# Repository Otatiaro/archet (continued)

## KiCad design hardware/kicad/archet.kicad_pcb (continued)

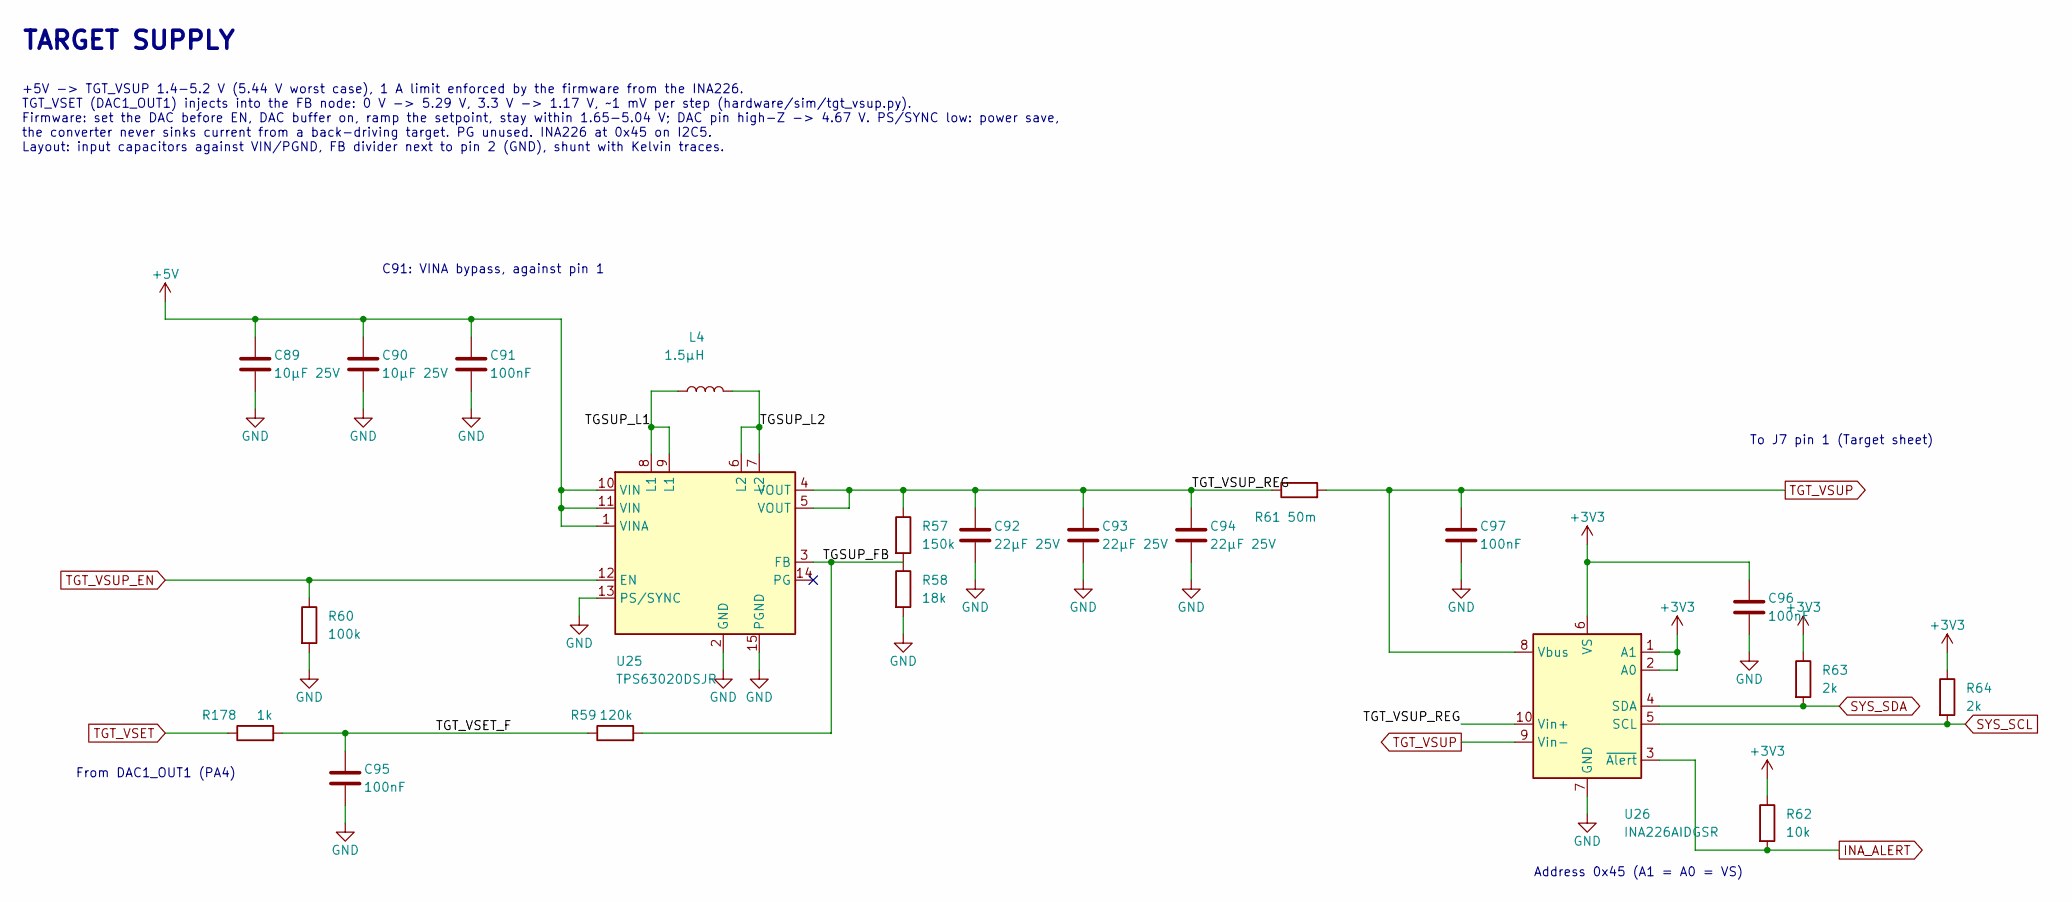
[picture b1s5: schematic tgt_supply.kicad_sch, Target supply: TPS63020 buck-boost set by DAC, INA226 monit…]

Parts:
C89, C90: 10µF 25V; C_0805_2012Metric; LCSC C15850
C91, C95, C96, C97: 100nF; C_0402_1005Metric; LCSC C307331
C92, C93, C94: 22µF 25V; C_1206_3216Metric; LCSC C12891
L4: 1.5µH; L_Changjiang_FXL0420; LCSC C167205
R57: 150k; R_0402_1005Metric; LCSC C25755
R58: 18k; R_0402_1005Metric; LCSC C25762
R59: 120k; R_0402_1005Metric; LCSC C25750
R60: 100k; R_0402_1005Metric; LCSC C25741
R61: 50m; R_1206_3216Metric; LCSC C844686
R62: 10k; R_0402_1005Metric; LCSC C25744
R63, R64: 2k; R_0402_1005Metric; LCSC C4109
R178: 1k; R_0402_1005Metric; LCSC C11702
U25: TPS63020DSJR; Texas_DSJ0014A_VSON-14_3x4mm_P0.5mm; LCSC C15483
U26: INA226AIDGSR; TSSOP-10_3x3mm_P0.5mm; LCSC C49851

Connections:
+3V3: C96.1, R62.1, R63.1, R64.1, U26.1 (A1), U26.2 (A0), U26.6 (VS); also elsewhere on the board
+5V: C89.1, C90.1, C91.1, U25.1 (VINA), U25.10 (VIN), U25.11 (VIN); also elsewhere on the board
/Target supply/TGSUP_FB: R57.2, R58.1, R59.2, U25.3 (FB)
/Target supply/TGSUP_L1: L4.1, U25.8 (L1), U25.9 (L1)
/Target supply/TGSUP_L2: L4.2, U25.6 (L2), U25.7 (L2)
/Target supply/TGT_VSET_F: C95.1, R59.1, R178.2
/Target supply/TGT_VSUP_REG: C92.1, C93.1, C94.1, R57.1, R61.1, U25.4 (VOUT), U25.5 (VOUT), U26.10 (Vin+)
GND: C89.2, C90.2, C91.2, C92.2, C93.2, C94.2, C95.2, C96.2, C97.2, R58.2, R60.2, U25.2 (GND), U25.13 (PS/SYNC), U25.15 (PGND), U26.7 (GND); also elsewhere on the board
INA_ALERT: R62.2, U26.3 (~Alert); also elsewhere on the board
SYS_SCL: R64.2, U26.5 (SCL); also elsewhere on the board
SYS_SDA: R63.2, U26.4 (SDA); also elsewhere on the board
TGT_VSET: R178.1; also elsewhere on the board
TGT_VSUP: C97.1, R61.2, U26.8 (Vbus), U26.9 (Vin-); also elsewhere on the board
TGT_VSUP_EN: R60.1, U25.12 (EN); also elsewhere on the board

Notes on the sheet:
TARGET SUPPLY
+5V -> TGT_VSUP 1.4-5.2 V (5.44 V worst case), 1 A limit enforced by the firmware from the INA226. TGT_VSET (DAC1_OUT1) injects into the FB node: 0 V -> 5.29 V, 3.3 V -> 1.17 V, ~1 mV per step (hardware/sim/tgt_vsup.py). Firmware: set the DAC before EN, DAC buffer on, ramp the setpoint, stay within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
C91: VINA bypass, against pin 1
From DAC1_OUT1 (PA4)
To J7 pin 1 (Target sheet)
Address 0x45 (A1 = A0 = VS)

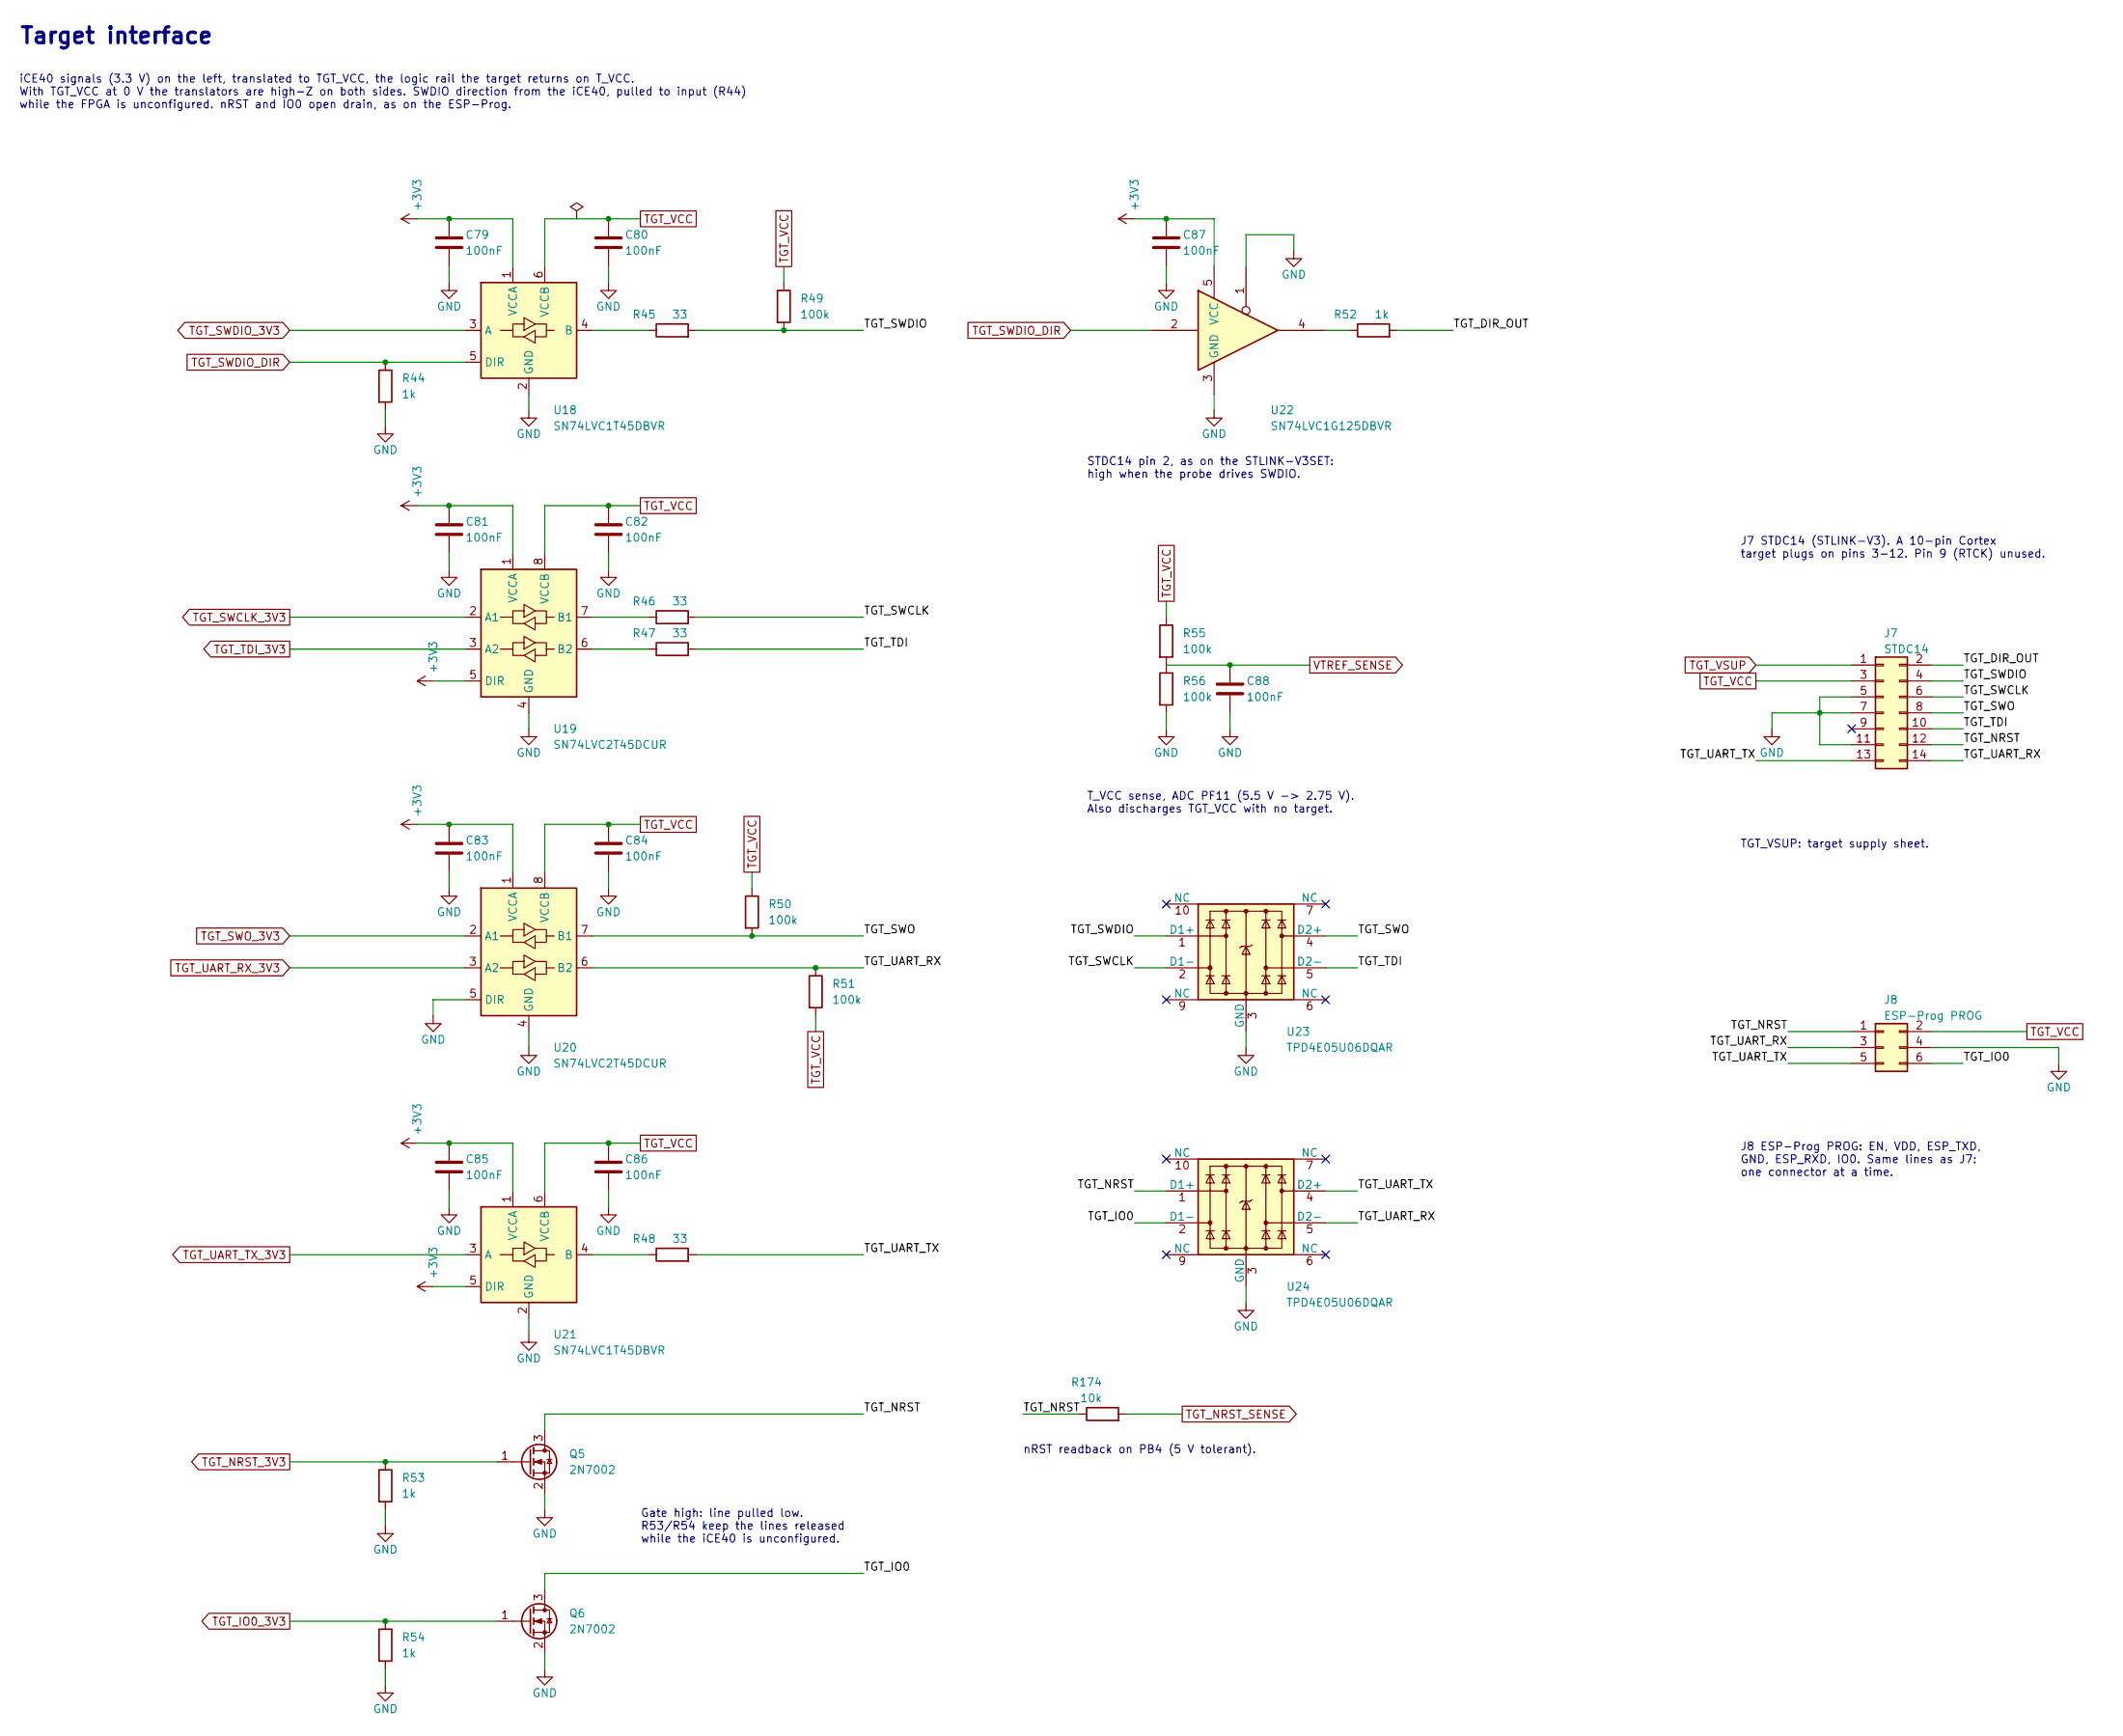
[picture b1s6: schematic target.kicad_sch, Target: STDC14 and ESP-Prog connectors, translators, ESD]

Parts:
C79, C80, C81, C82, C83, C84, C85, C86, C87, C88: 100nF; C_0402_1005Metric; LCSC C307331
J7: STDC14; FTSH-107-01-L-DV-K; LCSC C5307809
J8: ESP-Prog PROG; PinHeader_2x03_P2.54mm_Vertical; LCSC C492420
Q5, Q6: 2N7002; SOT-23; LCSC C8545
R44, R52, R53, R54: 1k; R_0402_1005Metric; LCSC C11702
R45, R46, R47, R48: 33; R_0402_1005Metric; LCSC C25105
R49, R50, R51, R55, R56: 100k; R_0402_1005Metric; LCSC C25741
R174: 10k; R_0402_1005Metric; LCSC C25744
U18, U21: SN74LVC1T45DBVR; SOT-23-6; LCSC C7843
U19, U20: SN74LVC2T45DCUR; VSSOP-8_2.3x2mm_P0.5mm; LCSC C15741
U22: SN74LVC1G125DBVR; SOT-23-5; LCSC C23654
U23, U24: TPD4E05U06DQAR; USON-10_2.5x1.0mm_P0.5mm; LCSC C138714

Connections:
+3V3: C79.1, C81.1, C83.1, C85.1, C87.1, U18.1 (VCCA), U19.1 (VCCA), U19.5 (DIR), U20.1 (VCCA), U21.1 (VCCA), U21.5 (DIR), U22.5 (VCC); also elsewhere on the board
/Target/TGT_DIR_OUT: J7.2, R52.2
/Target/TGT_IO0: J8.6, Q6.3 (D), U24.2 (D1-)
/Target/TGT_NRST: J7.12, J8.1, Q5.3 (D), R174.1, U24.1 (D1+)
/Target/TGT_SWCLK: J7.6, R46.2, U23.2 (D1-)
/Target/TGT_SWDIO: J7.4, R45.2, R49.2, U23.1 (D1+)
/Target/TGT_SWO: J7.8, R50.2, U20.7 (B1), U23.4 (D2+)
/Target/TGT_TDI: J7.10, R47.2, U23.5 (D2-)
/Target/TGT_UART_RX: J7.14, J8.3, R51.1, U20.6 (B2), U24.5 (D2-)
/Target/TGT_UART_TX: J7.13, J8.5, R48.2, U24.4 (D2+)
GND: C79.2, C80.2, C81.2, C82.2, C83.2, C84.2, C85.2, C86.2, C87.2, C88.2, J7.5, J7.7, J7.11, J8.4, Q5.2 (S), Q6.2 (S), R44.2, R53.2, R54.2, R56.2, U18.2 (GND), U19.4 (GND), U20.4 (GND), U20.5 (DIR), U21.2 (GND), U22.1, U22.3 (GND), U23.3 (GND), U23.8 (GND), U24.3 (GND), U24.8 (GND); also elsewhere on the board
unnamed: R52.1, U22.4
unnamed: R45.1, U18.4 (B)
unnamed: R46.1, U19.7 (B1)
unnamed: R47.1, U19.6 (B2)
unnamed: R48.1, U21.4 (B)
TGT_IO0_3V3: Q6.1 (G), R54.1; also elsewhere on the board
TGT_NRST_3V3: Q5.1 (G), R53.1; also elsewhere on the board
TGT_NRST_SENSE: R174.2; also elsewhere on the board
TGT_SWCLK_3V3: U19.2 (A1); also elsewhere on the board
TGT_SWDIO_3V3: U18.3 (A); also elsewhere on the board
TGT_SWDIO_DIR: R44.1, U18.5 (DIR), U22.2; also elsewhere on the board
TGT_SWO_3V3: U20.2 (A1); also elsewhere on the board
TGT_TDI_3V3: U19.3 (A2); also elsewhere on the board
TGT_UART_RX_3V3: U20.3 (A2); also elsewhere on the board
TGT_UART_TX_3V3: U21.3 (A); also elsewhere on the board
TGT_VCC: C80.1, C82.1, C84.1, C86.1, J7.3, J8.2, R49.1, R50.1, R51.2, R55.1, U18.6 (VCCB), U19.8 (VCCB), U20.8 (VCCB), U21.6 (VCCB)
TGT_VSUP: J7.1; also elsewhere on the board
VTREF_SENSE: C88.1, R55.2, R56.1; also elsewhere on the board

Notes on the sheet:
Target interface
iCE40 signals (3.3 V) on the left, translated to TGT_VCC, the logic rail the target returns on T_VCC. With TGT_VCC at 0 V the translators are high-Z on both sides. SWDIO direction from the iCE40, pulled to input (R44) while the FPGA is unconfigured. nRST and IO0 open drain, as on the ESP-Prog.
Gate high: line pulled low. R53/R54 keep the lines released while the iCE40 is unconfigured.
nRST readback on PB4 (5 V tolerant).
STDC14 pin 2, as on the STLINK-V3SET: high when the probe drives SWDIO.
T_VCC sense, ADC PF11 (5.5 V -> 2.75 V). Also discharges TGT_VCC with no target.
J7 STDC14 (STLINK-V3). A 10-pin Cortex target plugs on pins 3-12. Pin 9 (RTCK) unused.
J8 ESP-Prog PROG: EN, VDD, ESP_TXD, GND, ESP_RXD, IO0. Same lines as J7: one connector at a time.
TGT_VSUP: target supply sheet.

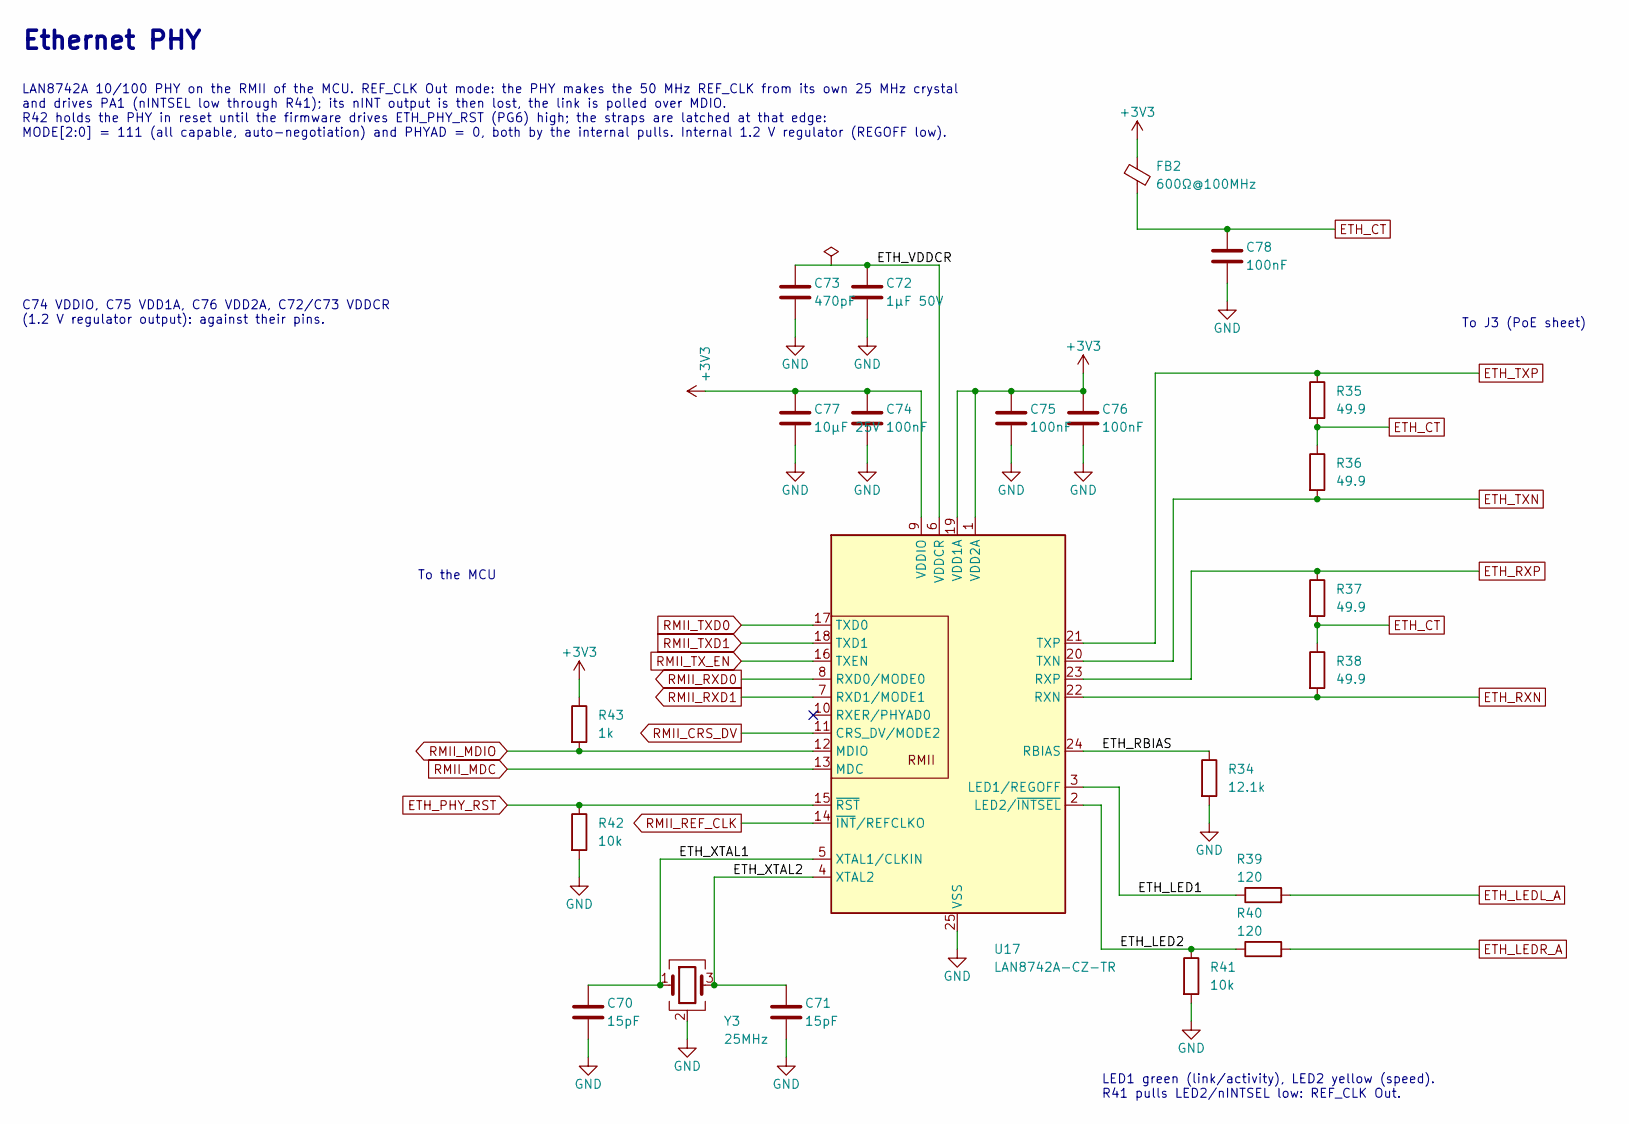
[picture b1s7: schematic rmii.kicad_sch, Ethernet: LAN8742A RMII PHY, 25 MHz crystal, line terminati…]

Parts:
C70, C71: 15pF; C_0402_1005Metric; LCSC C1548
C72: 1µF 50V; C_0603_1608Metric; LCSC C15849
C73: 470pF; C_0402_1005Metric; LCSC C1537
C74, C75, C76, C78: 100nF; C_0402_1005Metric; LCSC C307331
C77: 10µF 25V; C_0805_2012Metric; LCSC C15850
FB2: 600Ω@100MHz; L_0603_1608Metric; LCSC C1002
R34: 12.1k; R_0402_1005Metric; LCSC C25852
R35, R36, R37, R38: 49.9; R_0402_1005Metric; LCSC C25120
R39, R40: 120; R_0402_1005Metric; LCSC C25079
R41, R42: 10k; R_0402_1005Metric; LCSC C25744
R43: 1k; R_0402_1005Metric; LCSC C11702
U17: LAN8742A-CZ-TR; VQFN-24-1EP_4x4mm_P0.5mm_EP2.5x2.5mm; LCSC C621424
Y3: 25MHz; Crystal_SMD_3225-4Pin_3.2x2.5mm; LCSC C9006

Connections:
+3V3: C74.1, C75.1, C76.1, C77.1, FB2.1, R43.1, U17.1 (VDD2A), U17.9 (VDDIO), U17.19 (VDD1A); also elsewhere on the board
/Ethernet/ETH_LED1: R39.1, U17.3 (LED1/REGOFF)
/Ethernet/ETH_LED2: R40.1, R41.1, U17.2 (LED2/~INTSEL)
/Ethernet/ETH_RBIAS: R34.1, U17.24 (RBIAS)
/Ethernet/ETH_VDDCR: C72.1, C73.1, U17.6 (VDDCR)
/Ethernet/ETH_XTAL1: C70.1, U17.5 (XTAL1/CLKIN), Y3.1
/Ethernet/ETH_XTAL2: C71.1, U17.4 (XTAL2), Y3.3
ETH_CT: C78.1, FB2.2, R35.2, R36.1, R37.2, R38.1; also elsewhere on the board
ETH_LEDL_A: R39.2; also elsewhere on the board
ETH_LEDR_A: R40.2; also elsewhere on the board
ETH_PHY_RST: R42.1, U17.15 (~RST); also elsewhere on the board
ETH_RXN: R38.2, U17.22 (RXN); also elsewhere on the board
ETH_RXP: R37.1, U17.23 (RXP); also elsewhere on the board
ETH_TXN: R36.2, U17.20 (TXN); also elsewhere on the board
ETH_TXP: R35.1, U17.21 (TXP); also elsewhere on the board
GND: C70.2, C71.2, C72.2, C73.2, C74.2, C75.2, C76.2, C77.2, C78.2, R34.2, R41.2, R42.2, U17.25 (VSS), Y3.2 (G), Y3.4 (G); also elsewhere on the board
RMII_CRS_DV: U17.11 (CRS_DV/MODE2); also elsewhere on the board
RMII_MDC: U17.13 (MDC); also elsewhere on the board
RMII_MDIO: R43.2, U17.12 (MDIO); also elsewhere on the board
RMII_REF_CLK: U17.14 (~INT/REFCLKO); also elsewhere on the board
RMII_RXD0: U17.8 (RXD0/MODE0); also elsewhere on the board
RMII_RXD1: U17.7 (RXD1/MODE1); also elsewhere on the board
RMII_TXD0: U17.17 (TXD0); also elsewhere on the board
RMII_TXD1: U17.18 (TXD1); also elsewhere on the board
RMII_TX_EN: U17.16 (TXEN); also elsewhere on the board

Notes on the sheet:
Ethernet PHY
LAN8742A 10/100 PHY on the RMII of the MCU. REF_CLK Out mode: the PHY makes the 50 MHz REF_CLK from its own 25 MHz crystal and drives PA1 (nINTSEL low through R41); its nINT output is then lost, the link is polled over MDIO. R42 holds the PHY in reset until the firmware drives ETH_PHY_RST (PG6) hig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
To the MCU
C74 VDDIO, C75 VDD1A, C76 VDD2A, C72/C73 VDDCR (1.2 V regulator output): against their pins.
To J3 (PoE sheet)
LED1 green (link/activity), LED2 yellow (speed). R41 pulls LED2/nINTSEL low: REF_CLK Out.

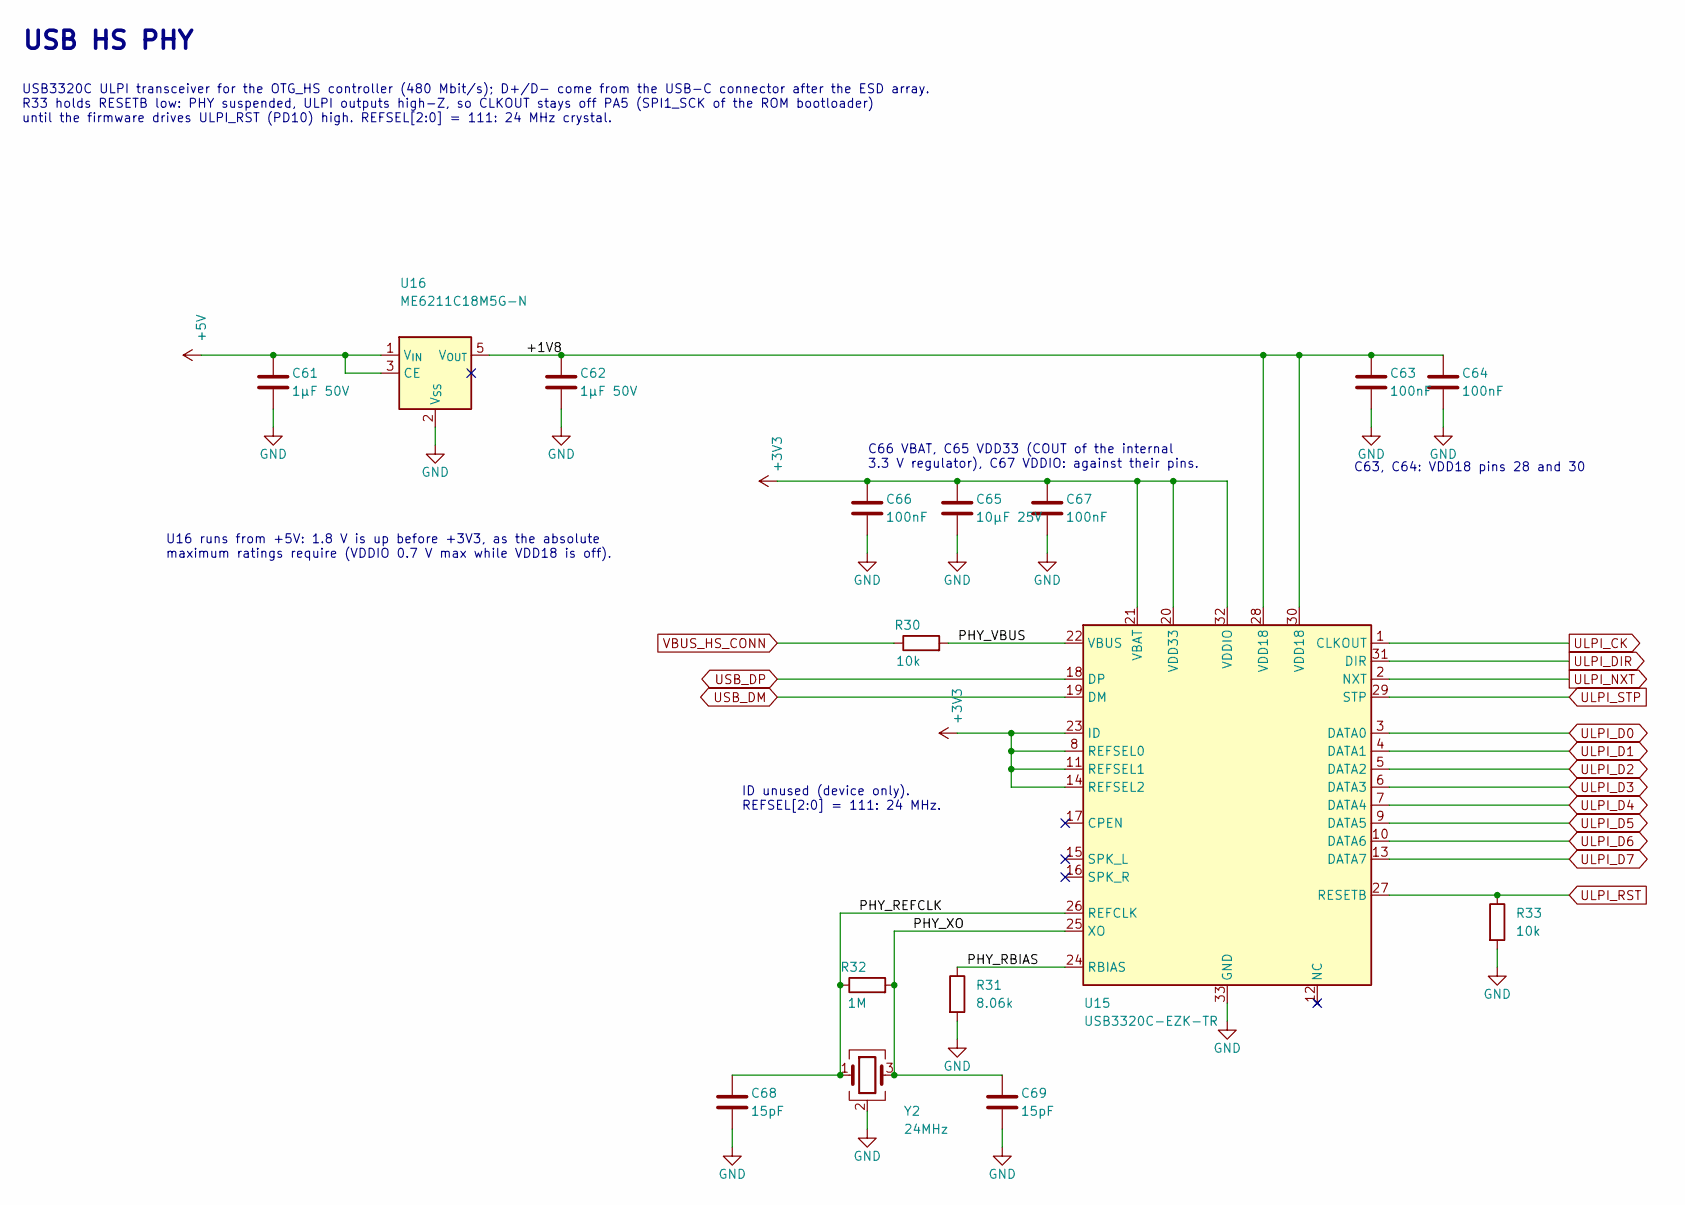
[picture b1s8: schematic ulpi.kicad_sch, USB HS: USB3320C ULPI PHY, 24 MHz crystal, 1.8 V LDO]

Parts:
C61, C62: 1µF 50V; C_0603_1608Metric; LCSC C15849
C63, C64, C66, C67: 100nF; C_0402_1005Metric; LCSC C307331
C65: 10µF 25V; C_0805_2012Metric; LCSC C15850
C68, C69: 15pF; C_0402_1005Metric; LCSC C1548
R30, R33: 10k; R_0402_1005Metric; LCSC C25744
R31: 8.06k; R_0402_1005Metric; LCSC C25923
R32: 1M; R_0402_1005Metric; LCSC C26083
U15: USB3320C-EZK-TR; QFN-32-1EP_5x5mm_P0.5mm_EP3.3x3.3mm; LCSC C132156
U16: ME6211C18M5G-N; SOT-23-5; LCSC C236671
Y2: 24MHz; Crystal_SMD_3225-4Pin_3.2x2.5mm; LCSC C70590

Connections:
+3V3: C65.1, C66.1, C67.1, U15.8 (REFSEL0), U15.11 (REFSEL1), U15.14 (REFSEL2), U15.20 (VDD33), U15.21 (VBAT), U15.23 (ID), U15.32 (VDDIO); also elsewhere on the board
+5V: C61.1, U16.1 (V_{IN}), U16.3 (CE); also elsewhere on the board
/USB HS/+1V8: C62.1, C63.1, C64.1, U15.28 (VDD18), U15.30 (VDD18), U16.5 (V_{OUT})
/USB HS/PHY_RBIAS: R31.1, U15.24 (RBIAS)
/USB HS/PHY_REFCLK: C68.1, R32.1, U15.26 (REFCLK), Y2.1
/USB HS/PHY_VBUS: R30.2, U15.22 (VBUS)
/USB HS/PHY_XO: C69.1, R32.2, U15.25 (XO), Y2.3
GND: C61.2, C62.2, C63.2, C64.2, C65.2, C66.2, C67.2, C68.2, C69.2, R31.2, R33.2, U15.33 (GND), U16.2 (V_{SS}), Y2.2 (G), Y2.4 (G); also elsewhere on the board
ULPI_CK: U15.1 (CLKOUT); also elsewhere on the board
ULPI_D0: U15.3 (DATA0); also elsewhere on the board
ULPI_D1: U15.4 (DATA1); also elsewhere on the board
ULPI_D2: U15.5 (DATA2); also elsewhere on the board
ULPI_D3: U15.6 (DATA3); also elsewhere on the board
ULPI_D4: U15.7 (DATA4); also elsewhere on the board
ULPI_D5: U15.9 (DATA5); also elsewhere on the board
ULPI_D6: U15.10 (DATA6); also elsewhere on the board
ULPI_D7: U15.13 (DATA7); also elsewhere on the board
ULPI_DIR: U15.31 (DIR); also elsewhere on the board
ULPI_NXT: U15.2 (NXT); also elsewhere on the board
ULPI_RST: R33.1, U15.27 (RESETB); also elsewhere on the board
ULPI_STP: U15.29 (STP); also elsewhere on the board
USB_DM: U15.19 (DM); also elsewhere on the board
USB_DP: U15.18 (DP); also elsewhere on the board
VBUS_HS_CONN: R30.1; also elsewhere on the board

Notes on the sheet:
USB HS PHY
USB3320C ULPI transceiver for the OTG_HS controller (480 Mbit/s); D+/D- come from the USB-C connector after the ESD array. R33 holds RESETB low: PHY suspended, ULPI outputs high-Z, so CLKOUT stays off PA5 (SPI1_SCK of the ROM bootloader) until the firmware drives ULPI_RST (PD10) high. REFSEL[2:0] =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
ID unused (device only). REFSEL[2:0] = 111: 24 MHz.
C66 VBAT, C65 VDD33 (COUT of the internal 3.3 V regulator), C67 VDDIO: against their pins.
C63, C64: VDD18 pins 28 and 30
U16 runs from +5V: 1.8 V is up before +3V3, as the absolute maximum ratings require (VDDIO 0.7 V max while VDD18 is off).

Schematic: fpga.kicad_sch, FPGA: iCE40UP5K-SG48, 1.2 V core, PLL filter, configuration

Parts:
C51, C52: 1µF 50V; C_0603_1608Metric; LCSC C15849
C53, C54, C56, C57, C58, C59, C60: 100nF; C_0402_1005Metric; LCSC C307331
C55: 10µF 25V; C_0805_2012Metric; LCSC C15850
R26: 100; R_0402_1005Metric; LCSC C25076
R27, R28, R29: 10k; R_0402_1005Metric; LCSC C25744
U13: iCE40UP5K-SG48I; QFN-48-1EP_7x7mm_P0.5mm_EP5.3x5.3mm; LCSC C2678152
U14: ME6211C12M5G-N; SOT-23-5; LCSC C236672

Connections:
+3V3: C57.1, C58.1, C59.1, C60.1, R28.1, R29.1, U13.1 (VCCIO_2), U13.22 (SPI_VCCIO1), U13.24 (VPP_2V5), U13.33 (VCCIO_0); also elsewhere on the board
+5V: C51.1, U14.1 (V_{IN}), U14.3 (CE); also elsewhere on the board
/FPGA/+1V2: C52.1, C53.1, C54.1, R26.1, U13.5 (VCC), U13.30 (VCC), U14.5 (V_{OUT})
/FPGA/VCCPLL: C55.1, C56.1, R26.2, U13.29 (VCCPLL)
FPGA_CDONE: R28.2, U13.7 (CDONE); also elsewhere on the board
FPGA_CRESET_B: R27.1, U13.8 (~CRESET); also elsewhere on the board
FPGA_IRQ: U13.18 (IOB_31b); also elsewhere on the board
FPGA_QSPI_CLK: U13.15 (IOB_34a_SPI_SCK); also elsewhere on the board
FPGA_QSPI_IO0: U13.17 (IOB_33b_SPI_SI); also elsewhere on the board
FPGA_QSPI_IO1: U13.14 (IOB_32a_SPI_SO); also elsewhere on the board
FPGA_QSPI_IO2: U13.12 (IOB_22a); also elsewhere on the board
FPGA_QSPI_IO3: U13.13 (IOB_24a); also elsewhere on the board
FPGA_QSPI_NCS: U13.16 (IOB_35b_SPI_SS); also elsewhere on the board
FPGA_REFCLK: U13.20 (IOB_25b_G3); also elsewhere on the board
GND: C51.2, C52.2, C53.2, C54.2, C55.2, C56.2, C57.2, C58.2, C59.2, C60.2, R27.2, U13.49 (GND), U14.2 (V_{SS}); also elsewhere on the board
LED_LINK: U13.40 (RGB1); also elsewhere on the board
LED_SPARE: U13.41 (RGB2); also elsewhere on the board
PPS: U13.19 (IOB_29b); also elsewhere on the board
SHIELD_IO0: U13.2 (IOB_6a); also elsewhere on the board
SHIELD_IO1: U13.3 (IOB_9b); also elsewhere on the board
SHIELD_IO2: U13.4 (IOB_8a); also elsewhere on the board
SHIELD_IO3: U13.6 (IOB_13b); also elsewhere on the board
SHIELD_IO4: U13.9 (IOB_16a); also elsewhere on the board
SHIELD_IO5: U13.10 (IOB_18a); also elsewhere on the board
SHIELD_IO6: U13.11 (IOB_20a); also elsewhere on the board
SHIELD_IO7: U13.37 (IOT_45a_G1); also elsewhere on the board
SHIELD_IO8: U13.38 (IOT_50b); also elsewhere on the board
SHIELD_IO9: U13.42 (IOT_51a); also elsewhere on the board
SHIELD_IO10: U13.43 (IOT_49a); also elsewhere on the board
SHIELD_IO11: U13.44 (IOB_3b_G6); also elsewhere on the board
SHIELD_IO12: U13.45 (IOB_5b); also elsewhere on the board
SHIELD_IO13: U13.46 (IOB_0a); also elsewhere on the board
SHIELD_IO14: U13.47 (IOB_2a); also elsewhere on the board
SHIELD_IO15: U13.48 (IOB_4a); also elsewhere on the board
SHIELD_OE_N: R29.2, U13.39 (RGB0); also elsewhere on the board
SYNC_IN: U13.23 (IOT_37a); also elsewhere on the board
SYNC_OUT: U13.21 (IOB_23b); also elsewhere on the board
TGT_IO0_3V3: U13.27 (IOT_38b); also elsewhere on the board
TGT_NRST_3V3: U13.28 (IOT_41a); also elsewhere on the board
TGT_SWCLK_3V3: U13.35 (IOT_46b_G0); also elsewhere on the board
TGT_SWDIO_3V3: U13.36 (IOT_48b); also elsewhere on the board
TGT_SWDIO_DIR: U13.34 (IOT_44b); also elsewhere on the board
TGT_SWO_3V3: U13.31 (IOT_42b); also elsewhere on the board
TGT_TDI_3V3: U13.32 (IOT_43a); also elsewhere on the board
TGT_UART_RX_3V3: U13.25 (IOT_36b); also elsewhere on the board
TGT_UART_TX_3V3: U13.26 (IOT_39a); also elsewhere on the board

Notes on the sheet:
FPGA
iCE40UP5K-SG48I, SPI slave configuration by the MCU over the QSPI pins. Pin assignment: hardware/fpga-pins.csv (checked by fpgacheck.py and nextpnr). Bank 1 (MCU, configuration) on the left, banks 0 and 2 (target translators, shield IOs) on the right. One 100 nF per supply pin, against the pin.
R27: FPGA held in reset (IOs high-Z) until the MCU releases CRESET_B, also in the ROM bootloader.
SHIELD_OE_N on RGB0 (open drain): R29 keeps the shield drivers off until the bitstream pulls it low. RGB1, RGB2: constant-current LED sinks (LINK, spare).
+1V2 from +5V: VCC and VCCPLL reach 0.5 V before SPI_VCCIO1 and VPP_2V5 (+3V3, buck from +5V), UltraPlus datasheet §4.5.
C53, C54: VCC pins 5 and 30
VCCPLL filter (Lattice UltraPlus development platform): 100 Ω, 10 µF, 100 nF against pin 29, even with the PLL unused. VPP_2V5 on +3V3: NVCM unused, SPI slave configuration.
